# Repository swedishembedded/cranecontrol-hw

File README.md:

# CraneControl Schematic and PCB

**Electronic hardware for controlling a vehicle mounted movie production crane**

	Copyright (c) 2019-2022 Martin Schröder, All rights reserved.

- Connect with me on LinkedIn: https://www.linkedin.com/in/martinschroder/
- Connect by email: martin.schroder@swedishembedded.com

This repository contains electical schematic and pcb layouts for boards that
can be used to control a movie production camera crane.

What does such a crane look like in practice? Well here is CraneControl boards
providing HMI and dual motor control function to FlyingBergman movie production
crane (click on images to watch the video):

[](http://www.youtube.com/watch?v=k-2InPx5LMA
"FlyingBergman")

[](http://www.youtube.com/watch?v=5sOf54V7gs8
"FlyingBergman on land")

[](http://www.youtube.com/watch?v=lv9wT3cRuf8
"FlyingBergman at sea")

[FlyingBergman](https://flyingbergman.se) crane is best known for being used for filming all car scenes in
2022 Netflix series "Clark".

[](http://www.youtube.com/watch?v=Xm6EU1w8b1s
"Clark")

If you are a movie producer and would like to order finished product then send
an email to info@swedishembedded.com and ask for more information. The complete
FlyingBergman setup also includes the crane assembly, HMI control panel for
mounting inside the vehicle and all necessary electronics.

## CraneControl platform

FlyingBergman is only one specific application of crane control hardware
design. CraneControl was originally designed to be a versatile solution capable
of advanced features like field oriented control of 2 60V PMSM motors at the
same time using the same microcontroller. It was also designed to provide
modern communication options like CAN-FD and EtherCAT.

In the case of FlyingBergman only a subset of these features was used - meaning
there is a lot of room to epand the use of this hardware for achieving more
complex control tasks in an industrial environment.

## Block diagram

## Schematic PDF

## Who is this for

This repository is for you if:

- You are a student of embedded systems courses at swedishembedded.com
  (https://swedishembedded.com/tag/training).

- You are building industrial control solutions and you would like to add
  support for advanced motor control (in this case you can also contract this
  task to Swedish Embedded Consulting Group. Book a call here:
  https://swedishembedded.com/book-call)

- You are simply curious about designing practical hardware and would like to
  learn from this project.

## License

You may use this design as inspiration for other designs as long as you develop
schematic and layout by yourself. You may also use this design as learning
materials for study.

If you would like to build a commercial product using this design then you can
contract Swedish Embedded Consulting Group to implement a specialized
hardware/software solution for you (send and email to
info@swedishembedded.com).

## Building

To generate gerbers for this design from command line you can use kibot
(https://github.com/INTI-CMNB/KiBot) with provided 'motordriver-2x.kibot.yaml'
file in this repository.

You can also edit this design in KiCad (version 6.0 or above).

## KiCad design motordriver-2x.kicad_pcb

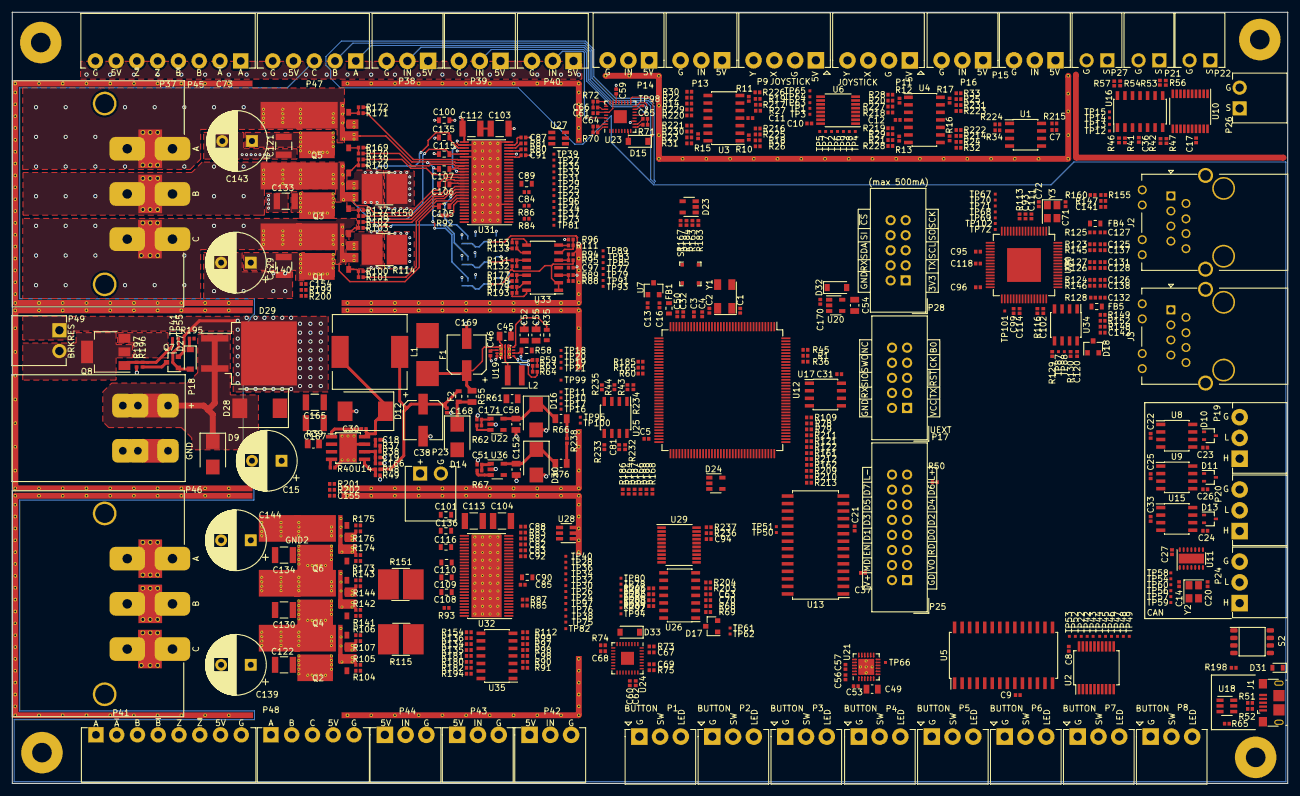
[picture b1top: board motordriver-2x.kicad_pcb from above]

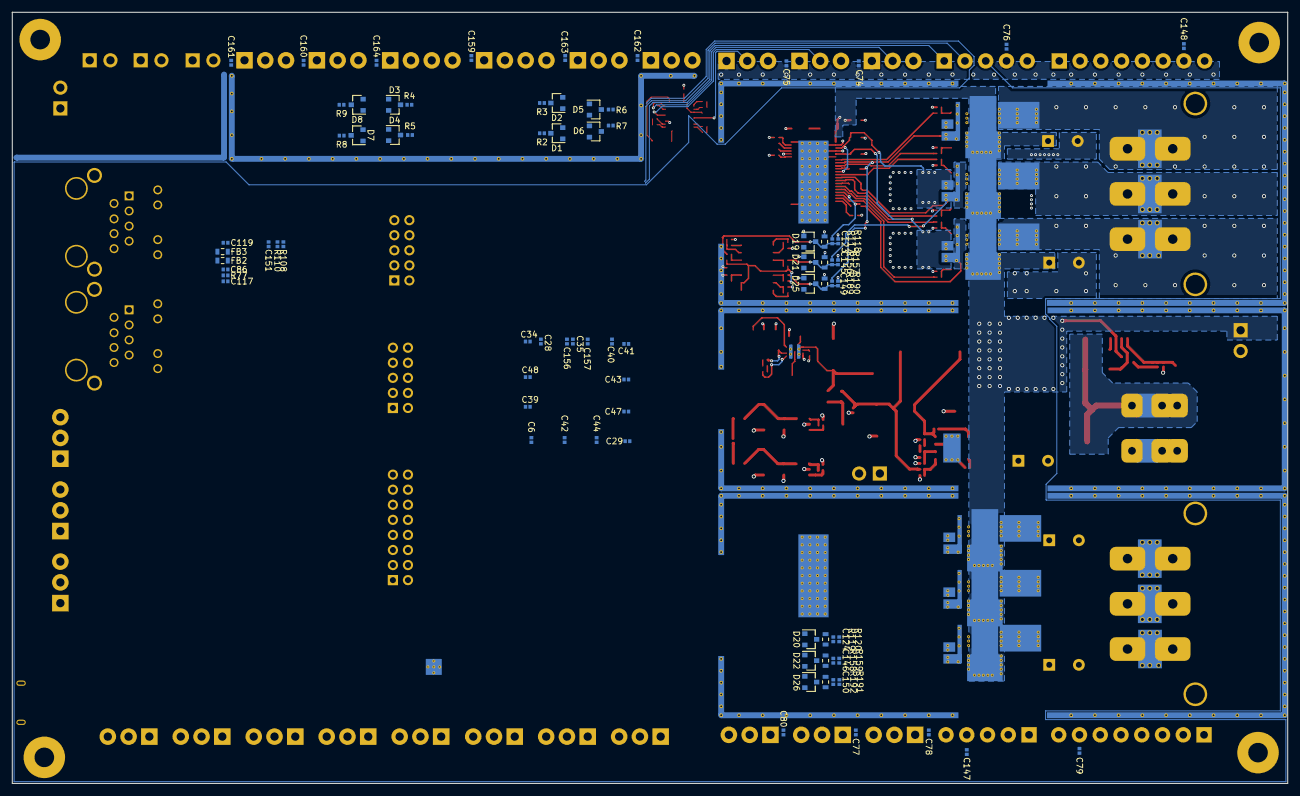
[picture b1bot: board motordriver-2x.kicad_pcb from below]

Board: 4 copper layers, 215.0 x 130.0 mm, 651 parts (79 on the bottom side), 453 nets.

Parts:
C1, C2, C14, C20, C71, C72, C125, C126, C127, C128, C131, C132, C137, C138: CAP_10pF_50V_0402; C_0402_1005Metric
C3, C4, C8, C9, C10, C11, C12, C16, C17, C21, C22, C23, C24, C25, C26, C27, C28, C29, C30, C31, C32, C33, C34, C35, C36, C39, C40, C41, C42, C43, C44, C46, C47, C48, C50, C59, C60, C61, C62, C63, C70, C82, C83, C86, C93, C94, C95, C96, C97, C98, C99, C102, C111, C114, C117, C118, C119, C120, C151, C154, C155, C156, C157: CAP_100nF_50V_0402; C_0402_1005Metric
C5, C6, C7, C13, C37, C51, C53, C56, C57, C73, C74, C75, C76, C77, C78, C79, C80, C81, C84, C85, C87, C88, C91, C92, C147, C148, C159, C160, C161, C162, C163, C164, C168, C170, C171: CAP_2.2uF_16V_0402; C_0402_1005Metric
C15, C139, C140, C143, C144: CAPP_220uF_63V_10x15_THT; CP_Radial_D10.0mm_P5.00mm
C18: CAP_27nF_16V_0402; C_0402_1005Metric
C19, C64, C65, C66, C67, C68, C69, C166: CAP_100pF_50V_0402; C_0402_1005Metric
C38, C169: CAPP_100uF_25V_6357; CP_Elec_6.3x5.7
C45, C49: CAP_10uF_25V_0805; C_0805_2012Metric
C52, C54, C55, C58, C152: CAP_22uF_10V_0805; C_0805_2012Metric
C89, C90: CAP_0.022uF_100V_0603; C_0603_1608Metric
C100, C101, C105, C106, C107, C108, C109, C110, C123, C124, C145, C146, C149, C150: CAP_100nF_100V_0603; C_0603_1608Metric
C103, C104, C112, C113, C121, C122, C129, C130, C133, C134, C165, C167: CAP_2.2uF_100V_1210; C_1210_3225Metric
C115, C116, C135, C136: CAP_1nF_100V_0603; C_0603_1608Metric
C141, C142: CAP_22nF_50V_0402; C_0402_1005Metric
D1, D2, D3, D4, D5, D6, D7, D8, D17, D18, D19, D20, D21, D22, D25, D26: D_BAT54S; SOT-23
D9: D_SMBJ48A; D_SMB
D10, D11, D13: D_ESDCAN03; SOT-323_SC-70
D12, D28: D_CDBC5100; D_SMC
D14: D_SMBJ12A; D_SMB
D15, D27, D32, D33: D_BAT54; D_SOD-123
D16, D30: D_SZ1SMB5913BT3G; D_SMB
D23, D24: D_TPD3E001; SOT-23-5
D29: D_STPS41H100; TO-263-2
D31: LED_RED_0603; LED_0603_1608Metric
F1: FUSE_3A_9750; Fuse_Littlefuse_9750
F2: FUSE_4A_0603; Fuse_0603_1608Metric
FB1, FB2, FB3, FB4, FB5: LB_220R_2A_0603; L_0603_1608Metric
GND1: GND_100X30
GND2, GND3: GND_MOTOR_DRIVER
GND4: GND_ANALOG_IN
GND5: GND_ANALOG_OUT
J1: USB_B_Micro; USB_Micro-B_GCT_USB3076-30-A
J2, J3: CONN_RJ45_MAG; RJ45_Tranformer
L1: L_33uH_4.2A_45mR; L_Wuerth_WE-PD-Typ-LS_1250x1250
L2: L_2.2uH_8A; L_Coilcraft_XxL4020
MT1, MT2, MT3, MT4: MOUNT_HOLE; MountingHole_3.2mm_M3_Pad
P1, P2, P3, P4, P5, P6, P7, P8: CONN_BUTTON
P9, P11: CONN_JOYSTICK
P13, P14, P15, P16, P38, P39, P40, P42, P43, P44: CONN_SENSOR
P17: CONN_DEBUG_2R; IDC-Header_2x05_P2.54mm_Vertical
P18: CONN_POWER_41A; PhoenixContact_Power41A_2,5_2-G-7,62_1x02_P7.62mm_Horizontal
P19, P20, P24: CONN_CAN
P21, P22, P26, P27: CONN_AN_OUT
P23: CONN_POWER_10A
P25: CONN_LCD
P28: CONN_UEXT
P37, P41: CONN_ENCODER
P45, P46: CONN_MOTOR; ANYTEK_7.62mm_2x_3P_32A
P47, P48: CONN_HALL
P49: CONN_BRKRES
Q1, Q2, Q3, Q4, Q5, Q6: Q_NMOS_2X_60V_63A; PowerPack-8x8-Dual
Q7: Q_PNP_BC856; SOT-23
Q8: Q_NMOS_BUK9875; SOT-223
R1, R2, R3, R4, R5, R6, R7, R8, R9, R38, R41, R42, R43, R44, R49, R53, R54, R60, R62, R63, R64, R67, R84, R85, R86, R87, R88, R89, R90, R91, R94, R95, R96, R97, R98, R99, R100, R103, R104, R107, R108, R110, R113, R116, R118, R120, R131, R132, R133, R134, R135, R136, R137, R140, R141, R144, R149, R157, R159, R160, R169, R172, R173, R176, R177, R178, R179, R180, R181, R182, R183, R184, R185, R186, R187, R188, R190, R192, R195, R196, R197, R199, R201, R203, R204, R205, R206, R207, R208: RES_10K_1%_0402; R_0402_1005Metric
R10, R11, R12, R13, R14, R15, R16, R17, R65, R147, R148: RES_0R_0402; R_0402_1005Metric
R18, R19, R20, R21, R22, R23, R24, R25: RES_1K5_1%_0402; R_0402_1005Metric
R26, R27, R28, R29, R30, R31, R32, R33, R36, R37, R45, R59, R80, R81, R82, R83, R129, R130: RES_3K_1%_0402; R_0402_1005Metric
R34, R214, R215, R216, R217, R218, R219, R220, R221, R222, R223, R224, R225, R226, R227, R228, R229, R230, R231, R232, R233, R234, R235, R236, R237, R238: RES_NOFIT_0402; R_0402_1005Metric
R35, R58: RES_147k_1%_0603; R_0603_1608Metric
R39, R55, R61, R66, R76: RES_10mOhm_1%; R_0805_2012Metric
R40, R48, R68, R117, R119, R156, R158, R189, R191: RES_137K_1%_0402; R_0402_1005Metric
R46, R47, R56, R57, R69, R111, R112, R153, R154, R163, R164, R165, R166, R167, R168, R193, R194: RES_5K_1%_0402; R_0402_1005Metric
R50, R198: RES_470R_1%_0402; R_0402_1005Metric
R51, R52, R101, R102, R105, R106, R138, R139, R142, R143, R170, R171, R174, R175: RES_22R_1%_0402; R_0402_1005Metric
R70, R71, R72, R73, R74, R75, R78, R79, R109, R121, R122, R152, R155, R161, R162, R209, R210, R211, R212, R213: RES_270R_1%_0402; R_0402_1005Metric
R77: RES_12.1K_1%_0402; R_0402_1005Metric
R92, R93: RES_1M_1%_0402; R_0402_1005Metric
R114, R115, R150, R151: RES_5mR_1%_10W; R_2818_7146Metric
R123, R124, R125, R126, R127, R128, R145, R146: RES_49.9_0.1%_0402; R_0402_1005Metric
R200, R202: RES_NTC_10K_402; R_0402_1005Metric
S1: SW_BTN_3.7x3.7; SW_PTS540
S2: SW_DIP_4P; SOIC127P670X145-8N
TP1, TP2, TP3, TP4, TP5, TP6, TP7, TP8, TP9, TP10, TP11, TP12, TP13, TP14, TP15, TP16, TP17, TP18, TP19, TP20, TP21, TP22, TP23, TP24, TP25, TP26, TP27, TP28, TP29, TP30, TP31, TP32, TP33, TP34, TP35, TP36, TP37, TP38, TP39, TP40, TP41, TP42, TP43, TP44, TP45, TP46, TP47, TP48, TP49, TP50, TP51, TP52, TP53, TP54, TP55, TP56, TP57, TP58, TP59, TP60, TP61, TP62, TP63, TP64, TP65, TP66, TP67, TP68, TP69, TP70, TP71, TP72, TP73, TP74, TP75, TP76, TP77, TP78, TP79, TP80, TP81, TP82, TP83, TP84, TP85, TP86, TP87, TP88, TP89, TP90, TP91, TP92, TP93, TP94, TP95, TP96, TP97, TP98, TP99, TP100, TP101, TP102: Test_Point; TestPoint_Pad_0.5x0.5mm
U1, U25: IC_MIC2026; SOIC-8_3.9x4.9mm_P1.27mm
U2: IC_MAX6818; SSOP-20_5.3x7.2mm_P0.65mm
U3, U4, U16, U26, U33, U35: IC_TLV2474; SOIC-14_3.9x8.7mm_P1.27mm
U5, U13: IC_MCP23S17; SOIC-28W_7.5x17.9mm_P1.27mm
U6: IC_SN74LV4051; TSSOP-16_4.4x5mm_P0.65mm
U7: IC_NCP51460SN33T1G; SOT-23
U8, U9, U15: IC_TJA1044GT3; SOIC-8_3.9x4.9mm_P1.27mm
U10, U29: IC_MCP4461; TSSOP-20_4.4x6.5mm_P0.65mm
U11: IC_MCP2517FD-xJHA; DFN-14-1EP_3x4.5mm_P0.65mm_EP1.65x4.25mm
U12: IC_STM32F429ZET6; LQFP-144_20x20mm_P0.5mm
U14: IC_TPS54360DDA; TI_SO-PowerPAD-8
U17, U34: IC_M24C16; SOIC-8_3.9x4.9mm_P1.27mm
U18, U27, U28: IC_USBLC6-2; SOT-23-6L
U19: IC_TPS62147RGXR; RGX_VQFN-11
U20, U22, U36: IC_TLV75533; SOT-23-5
U21: IC_LP55231; WQFN-24-1EP_4x4mm_P0.5mm_EP2.7x2.7mm_Thermal
U23, U24: IC_MAX14890; QFN-32-1EP_5x5mm_P0.5mm_EP2.20x2.20mm
U30: IC_LAN9252; TQFP-64-1EP_10x10mm_P0.5mm_EP5.7x5.7mm
U31, U32: IC_DRV8302; HTSSOP-56-PowerPAD_6.2x14.1mm_P0.5mm_EP3.61x6.35mm
Y1: XTAL_8Mhz_5032; Crystal_ABM3B_5032-4Pin_5.0x3.2mm
Y2: XTAL_20MHz_3225; Crystal_SMD_3225-4Pin_3.2x2.5mm
Y3: XTAL_25MHz_3225; Crystal_SMD_3225-4Pin_3.2x2.5mm

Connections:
AINPWEN: R224.2, U1.1, U12.12
AIN_OC: R34.1, U1.2, U5.21
AIN_VDD_5V: C159.1, C160.1, C161.1, C162.1, C163.1, C164.1, P9.1, P11.1, P13.1, P14.1, P15.1, P16.1, R215.1, U1.8
AP_RESET1: U5.25, U10.15
AP_SCL1: R45.1, U10.5, U12.139, U17.6, U21.9, U29.5
AP_SDA1: R36.1, U10.6, U12.137, U17.5, U21.8, U29.6
AP_WP1: U5.24, U10.14
BLED_EN: U12.58, U21.5
BLED_INT: U12.67, U21.7
BOOT0: P17.9, R1.2, U12.138
CANFD_CS: TP60.1, U11.13, U12.125
CANFD_INT: TP59.1, U11.4, U12.124
CANFD_MISO: TP70.1, U11.12, U12.127, U30.13
CANFD_MOSI: TP69.1, U11.11, U12.129, U30.17
CANFD_SCK: TP72.1, U11.10, U12.128, U30.19
CANFD_SOF: U11.3, U12.93
CAN_RX1: U8.4, U12.114
CAN_RX2: U9.4, U12.73
CAN_TX1: U8.1, U12.115
CAN_TX2: U9.1, U12.74
DC_CAL1: TP74.1, U12.89, U31.12
DC_CAL2: TP76.1, U12.90, U32.12
ECAT_CS: TP71.1, U12.126, U30.50
ECAT_IRQ: TP68.1, U12.92, U30.44
ECAT_RESET: TP67.1, U12.91, U30.11
EE_WEN: U12.140, U17.7
ENC1VDD5V: C73.2, C74.2, C75.2, C76.2, C148.1, P37.7, P38.1, P39.1, P40.1, P47.4, R232.1, U25.8
ENC2VDD5V: C77.2, C78.2, C79.2, C80.2, C147.1, P41.7, P42.1, P43.1, P44.1, P48.4, R233.1, U25.5
ENCA1: U12.110, U23.1
ENCA2: U12.81, U24.1
ENCB1: U12.133, U23.8
ENCB2: U12.82, U24.8
ENCCS1: U12.118, U23.4
ENCCS2: U12.86, U24.4
ENCMISO1: R121.1, U23.3
ENCMISO2: R122.1, U24.3
ENCMOSI1: R162.1, U23.6
ENCMOSI2: R209.1, U24.6
ENCOC1: R43.2, U5.22, U25.2
ENCOC2: R44.2, U5.23, U25.3
ENCPWEN1: R234.2, U12.69, U25.1
ENCPWEN2: R235.2, U12.70, U25.4
ENCSCK1: R78.1, U23.5
ENCSCK2: R79.1, U24.5
ENCSH1: U12.119, U23.28
ENCSH2: U12.80, U24.28
ENCZ1: U12.77, U23.24
ENCZ2: U12.85, U24.24
EN_GATE1: TP96.1, U12.117, U31.16
EN_GATE2: TP97.1, U12.116, U32.16
FAULT1: R86.1, U12.122, U31.6
FAULT2: R87.1, U12.123, U32.6
GA1_N: R102.2, U31.45
GA1_P: R101.2, U31.47
GAIN1: TP73.1, U12.53, U31.10
GAIN2: TP75.1, U12.55, U32.10
GB1_N: R139.2, U31.40
GB1_P: R138.2, U31.42
GC1_N: R171.2, U31.35
GC1_P: R170.2, U31.37
GHA2: R105.2, U32.47
GHB2: R142.2, U32.42
GHC2: R174.2, U32.37
GLA2: R106.2, U32.45
GLB2: R143.2, U32.40
GLC2: R175.2, U32.35
GND: C1.2, C2.2, C3.2, C4.2, C5.2, C6.2, C7.2, C8.2, C9.2, C10.1, C11.1, C12.1, C13.2, C14.1, C15.2, C16.2, C17.1, C18.2, C19.2, C20.2, C21.2, C22.1, C23.1, C24.1, C25.1, C26.1, C27.1, C28.2, C29.2, C31.1, C32.2, C33.2, C34.2, C35.2, C36.1, C37.2, C38.2, C39.2, C40.2, C41.2, C42.2, C43.2, C44.2, C45.2, C46.2, C47.2, C48.2, C49.2, C50.2, C51.1, C52.2, C54.2, C55.2, C57.2, C58.2, C59.2, C60.2, C61.2, C62.2, C63.2, C70.1, C71.1, C72.1, C73.1, C74.1, C75.1, C76.1, C77.1, C78.1, C79.1, C80.1, C81.2, C82.2, C83.2, C84.2, C85.2, C86.1, C87.2, C88.2, C91.2, C92.2, C93.2, C94.1, C95.2, C96.2, C97.1, C98.1, C99.2, C100.2, C101.2, C102.2, C103.2, C104.2, C111.2, C114.2, C115.2, C116.2, C117.1, C118.2, C119.2, C120.1, C121.2, C122.2, C123.2, C124.2, C125.1, C126.2, C127.1, C128.2, C129.2, C130.2, C131.1, C132.2, C133.2, C134.2, C135.2, C136.2, C137.1, C138.2, C139.2, C140.2, C141.2, C142.1, C143.2, C144.2, C145.2, C146.2, C147.2, C148.2, C149.2, C150.2, C151.2, C152.2, C154.1, C155.1, C156.1, C157.1, C159.2, C160.2, C161.2, C162.2, C163.2, C164.2, C165.2, C166.2, C167.2, C168.2, C169.2, C170.2, C171.1, D1.1, D2.1, D3.1, D4.1, D5.1, D6.1, D7.1, D8.1, D9.2, D10.3, D11.3, D12.2, D13.3, D14.2, D16.2, D17.1, D19.1, D20.1, D21.1, D22.1, D23.3, D24.3, D25.1, D26.1, D30.2, D31.1, GND1.1, GND2.1, GND3.1, GND4.1, GND5.1, J1.5, J1.6, J2.8, J2.9, J3.8, J3.9, P1.1, P2.1, P3.1, P4.1, P5.1, P6.1, P7.1, P8.1, P9.2, P11.2, P13.3, P14.3, P15.3, P16.3, P17.2, P18.2, P19.3, P20.3, P21.2, P22.2, P23.2, P24.3, P25.1, P25.16, P26.2, P27.2, P28.2, P37.8, P38.3, P39.3, P40.3, P41.8, P42.3, P43.3, P44.3, P47.5, P48.5, Q5.3, Q6.3, Q8.3, R1.1, R26.2, R27.2, R28.2, R29.2, R30.2, R31.2, R32.2, R33.2, R40.2, R41.2, R42.2, R49.2, R53.2, R54.2, R60.2, R64.2, R69.1, R77.2, R89.1, R91.1, R92.1, R93.1, R96.2, R99.2, R100.2, R103.2, R104.2, R107.2, R108.1, R110.1, R113.1, R114.1, R115.1, R116.1, R118.1, R120.1, R133.2, R136.2, R137.2, R140.2, R141.2, R144.2, R149.1, R150.2, R151.2, R157.1, R159.1, R160.1, R169.2, R172.2, R173.2, R176.2, R179.2, R182.2, R183.1, R184.1, R185.1, R186.1, R187.1, R188.1, R190.1, R192.1, R197.2, R200.2, R202.2, R204.1, R206.1, R208.1, R214.1, R225.1, R226.1, R227.1, R228.1, R229.1, R230.1, R231.1, S1.1, S1.2, S2.1, S2.2, S2.3, S2.4, U1.6, U2.10, U3.11, U4.11, U5.10, U5.15, U5.16, U5.17, U6.6, U6.7, U6.8, U7.3, U8.2, U8.8, U9.2, U9.8, U10.3, U10.4, U10.7, U10.8, U10.13, U10.16, U10.18, U11.7, U11.15, U12.16, U12.31, U12.38, U12.51, U12.61, U12.83, U12.94, U12.107, U12.120, U12.130, U13.10, U13.15, U13.16, U13.17, U14.7, U14.9, U15.2, U16.11, U17.1, U17.2, U17.3, U17.4, U18.2, U19.3, U19.4, U19.10, U19.11, U20.2, U21.4, U21.6, U21.10, U21.20, U21.21, U21.25, U22.2, U23.11, U23.33, U24.11, U24.33, U25.6, U26.11, U27.2, U28.2, U29.3, U29.7, U29.8, U29.13, U29.16, U29.18, U30.4, U30.41, U30.65, U31.7, U31.8, U31.28, U31.30, U31.32, U31.34, U31.57, U32.7, U32.8, U32.28, U32.30, U32.32, U32.34, U32.57, U33.11, U34.1, U34.2, U34.3, U34.4, U34.7, U35.11, U36.2
GPEX_CS: U12.136, U13.11
GPEX_INTA: TP50.1, U12.21, U13.20
GPEX_INTB: TP51.1, U12.22, U13.19
GPEX_MISO: R212.1, U13.14
GPEX_MOSI: R213.1, U13.13
GPEX_RESET: U12.49, U13.18
GPEX_SCK: R211.1, U13.12
GPIO_CS: U5.11, U12.88
GPIO_INTA: TP52.1, U5.20, U12.57
GPIO_INTB: TP53.1, U5.19, U12.87
GPIO_MISO: R161.1, U5.14
GPIO_MOSI: R210.1, U5.13
GPIO_RESET: U5.18, U12.56
GPIO_SCK: R109.1, U5.12
HALL_A1: D23.1, R163.2, R183.2, U12.134
HALL_A2: D24.1, R164.2, R186.2, U12.34
HALL_B1: D23.2, R167.2, R184.2, U12.135
HALL_B2: D24.2, R166.2, R187.2, U12.35
HALL_C1: D23.4, R165.2, R185.2, U12.46
HALL_C2: D24.4, R168.2, R188.2, U12.36
INHA1: TP23.1, U12.60, U31.17
INHA2: TP24.1, U12.96, U32.17
INHB1: TP29.1, U12.64, U31.19
INHB2: TP30.1, U12.97, U32.19
INHC1: TP33.1, U12.66, U31.21
INHC2: TP34.1, U12.98, U32.21
INLA1: TP25.1, U12.59, U31.18
INLA2: TP26.1, U12.43, U32.18
INLB1: TP31.1, U12.63, U31.20
INLB2: TP32.1, U12.75, U32.20
INLC1: TP35.1, U12.65, U31.22
INLC2: TP36.1, U12.76, U32.22
LCD_D0: P25.7, U13.1
LCD_D1: P25.8, U13.2
LCD_D2: P25.9, U13.3
LCD_D3: P25.10, U13.4
LCD_D4: P25.11, U13.5
LCD_D5: P25.12, U13.6
LCD_D6: P25.13, U13.7
LCD_D7: P25.14, U13.8
LCD_EN: P25.6, U13.23
LCD_LED: R50.2, U13.24
LCD_MDATA: P25.4, U13.21
LCD_READ: P25.5, U13.22
LCD_VO: P25.3, U29.9
LED_OUT1: P1.3, U21.19
LED_OUT2: P2.3, U21.18
LED_OUT3: P3.3, U21.17
LED_OUT4: P4.3, U21.16
LED_OUT5: P5.3, U21.15
LED_OUT6: P6.3, U21.14
LED_OUT7: P7.3, U21.13
LED_OUT8: P8.3, U21.12
MOC1: U12.50, U31.9
MOC2: U12.54, U32.9
MOCP_RESET: U5.26, U29.15
MOCP_WP: U5.27, U29.14
MOTOR1_BRKIN: D15.2, U12.68, U23.7
MOTOR2_BRKIN: D33.2, U12.42, U24.7
NRST: C4.1, P17.5, S1.3, S1.4, U12.25
unnamed: C1.1, U12.23, Y1.1
unnamed: C2.1, U12.24, Y1.3
unnamed: C5.1, U12.71
unnamed: C6.1, U12.106
unnamed: C14.2, U11.5, Y2.1
unnamed: C15.1, D28.1, R39.2, TP10.1
unnamed: C18.1, R37.2
unnamed: C20.1, U11.6, Y2.3
unnamed: C30.1, D12.1, L1.1, U14.8
unnamed: C30.2, U14.1
unnamed: C32.1, C50.1, FB1.2, U12.32, U12.33
unnamed: C46.1, U19.9
unnamed: C52.1, C55.1, L2.2, R35.1, R58.1, R61.2, TP19.1, U19.6
unnamed: C53.1, U21.1
unnamed: C53.2, U21.23
unnamed: C54.1, D32.2, P28.1, U20.5
unnamed: C56.1, U21.24
unnamed: C56.2, U21.2
unnamed: C57.1, U21.22
unnamed: C58.1, D16.1, R66.2, TP21.1, U22.5
unnamed: C63.1, D17.3, R68.2, R69.2, TP61.1, U26.3
unnamed: C64.1, R70.2
unnamed: C64.2, P37.2, U23.31
unnamed: C65.1, R71.2
unnamed: C65.2, P37.4, U23.10
unnamed: C66.1, R72.2
unnamed: C66.2, P37.6, U23.26
unnamed: C67.1, R73.2
unnamed: C67.2, P41.2, U24.31
unnamed: C68.1, R74.2
unnamed: C68.2, P41.4, U24.10
unnamed: C69.1, R75.2
unnamed: C69.2, P41.6, U24.26
unnamed: C71.2, U30.1, Y3.3
unnamed: C72.2, U30.2, Y3.1
unnamed: C84.1, U31.13
unnamed: C85.1, U32.13
unnamed: C86.2, FB2.1, U30.58
unnamed: C87.1, U31.27
unnamed: C88.1, U32.27
unnamed: C89.1, U31.15
unnamed: C89.2, U31.14
unnamed: C90.1, U32.15
unnamed: C90.2, U32.14
unnamed: C91.1, U31.23
unnamed: C92.1, U32.23
unnamed: C103.1, C112.2
unnamed: C104.1, C113.2
unnamed: C105.1, U31.48
unnamed: C106.1, U31.43
unnamed: C107.1, U31.38
unnamed: C108.1, U32.48
unnamed: C109.1, U32.43
unnamed: C110.1, U32.38
unnamed: C114.1, C118.1, C151.1, FB3.2, U30.6, U30.24, U30.38
unnamed: C117.2, FB5.2, R124.2, R126.2, R128.2, R146.2, R148.1, U30.51
unnamed: C119.1, FB4.1, R123.1, R125.1, R127.1, R145.1, R147.2, U30.64
unnamed: C120.2, D18.3, U34.8
unnamed: C125.2, J2.1, R123.2, U30.62
unnamed: C126.1, J3.6, R124.1, U30.54
unnamed: C127.2, J2.3, R125.2, U30.63
unnamed: C128.1, J3.4, R126.1, U30.55
unnamed: C131.2, J2.4, R127.2, U30.60
unnamed: C132.1, J3.3, R128.1, U30.52
unnamed: C137.2, J2.6, R145.2, U30.61
unnamed: C138.1, J3.1, R146.1, U30.53
unnamed: C141.1, J2.2, J2.5, R147.1
unnamed: C142.2, J3.2, J3.5, R148.2
unnamed: C152.1, D30.1, R76.2, TP99.1, U36.5
unnamed: C165.1, C167.1, R39.1, TP11.1, U14.2
unnamed: C19.1, C166.1, R38.1, U14.6
unnamed: C38.1, C168.1, F2.2, L1.2, R48.1
unnamed: C45.1, C169.1, F1.1, R55.2, TP16.1, U19.1, U19.8
unnamed: D1.3, R2.1, R216.2, U3.3
unnamed: D2.3, R3.1, R217.2, U3.5
unnamed: D3.3, R4.1, R218.2, U4.3
unnamed: D4.3, R5.1, R219.2, U4.5
unnamed: D5.3, R6.1, R220.2, U3.10
unnamed: D6.3, R7.1, R221.2, U3.12
unnamed: D7.3, R8.1, R222.2, U4.10
unnamed: D8.3, R9.1, R223.2, U4.12
unnamed: D10.1, P19.2, U8.7
unnamed: D10.2, P19.1, U8.6
unnamed: D11.1, P20.2, U9.7
unnamed: D11.2, P20.1, U9.6
unnamed: D13.1, P24.2, U15.7
unnamed: D13.2, P24.1, U15.6
unnamed: D14.1, F2.1, R55.1, TP17.1
unnamed: D15.1, U23.17
unnamed: D27.1, R195.1
unnamed: D27.2, Q7.1, TP55.1
unnamed: D31.2, R198.2
unnamed: D33.1, U24.17
unnamed: F1.2, P23.1
unnamed: FB3.1, U30.56, U30.59
unnamed: J1.1, R65.2, U18.5
unnamed: J1.2, R52.2
unnamed: J1.3, R51.2
unnamed: J2.10, R155.1
unnamed: J3.10, R152.1
unnamed: L2.1, U19.2
unnamed: P9.3, R2.2
unnamed: P9.4, R3.2
unnamed: P11.3, R4.2
unnamed: P11.4, R5.2
unnamed: P13.2, R6.2
unnamed: P14.2, R7.2
unnamed: P15.2, R8.2
unnamed: P16.2, R9.2
unnamed: P21.1, R46.1, U16.1
unnamed: P22.1, R47.1, U16.7
unnamed: P25.15, R50.1
unnamed: P26.1, R56.1, U16.8
unnamed: P27.1, R57.1, U16.14
unnamed: P37.1, R70.1, U23.32
unnamed: P37.3, R71.1, U23.9
unnamed: P37.5, R72.1, U23.25
unnamed: P38.2, U23.16
unnamed: P39.2, U23.13
unnamed: P40.2, U23.29
unnamed: P41.1, R73.1, U24.32
unnamed: P41.3, R74.1, U24.9
unnamed: P41.5, R75.1, U24.25
unnamed: P42.2, U24.16
unnamed: P43.2, U24.13
unnamed: P44.2, U24.29
unnamed: P47.1, R163.1
unnamed: P47.2, R167.1
unnamed: P47.3, R165.1
unnamed: P48.1, R164.1
unnamed: P48.2, R166.1
unnamed: P48.3, R168.1
unnamed: P49.2, Q8.2, Q8.4
unnamed: Q1.1, R100.1, R101.1
unnamed: Q1.4, R102.1, R103.1
unnamed: Q2.1, R104.1, R105.1
unnamed: Q2.4, R106.1, R107.1
unnamed: Q3.1, R137.1, R138.1
unnamed: Q3.4, R139.1, R140.1
unnamed: Q4.1, R141.1, R142.1
unnamed: Q4.4, R143.1, R144.1
unnamed: Q5.1, R169.1, R170.1
unnamed: Q5.4, R171.1, R172.1
unnamed: Q6.1, R173.1, R174.1
unnamed: Q6.4, R175.1, R176.1
unnamed: Q7.3, R196.2
unnamed: Q8.1, R196.1, R197.1, TP41.1
unnamed: R10.1, R18.2, R216.1, R225.2, U3.1
unnamed: R10.2, U3.2
unnamed: R11.1, R19.2, R217.1, R226.2, U3.7
unnamed: R11.2, U3.6
unnamed: R12.1, R20.2, R218.1, R227.2, U4.1
unnamed: R12.2, U4.2
unnamed: R13.1, R21.2, R219.1, R228.2, U4.7
unnamed: R13.2, U4.6
unnamed: R14.1, R22.2, R220.1, R229.2, U3.8
unnamed: R14.2, U3.9
unnamed: R15.1, R23.2, R221.1, R230.2, U3.14
unnamed: R15.2, U3.13
unnamed: R16.1, R24.2, R214.2, R222.1, U4.8
unnamed: R16.2, U4.9
unnamed: R17.1, R25.2, R223.1, R231.2, U4.14
unnamed: R17.2, U4.13
unnamed: R18.1, R26.1, TP7.1, U6.13
unnamed: R19.1, R27.1, TP5.1, U6.14
unnamed: R20.1, R28.1, TP3.1, U6.15
unnamed: R21.1, R29.1, TP1.1, U6.12
unnamed: R22.1, R30.1, TP2.1, U6.1
unnamed: R23.1, R31.1, TP4.1, U6.5
unnamed: R24.1, R32.1, TP6.1, U6.2
unnamed: R25.1, R33.1, TP8.1, U6.4
unnamed: R35.2, TP18.1, U19.7
unnamed: R37.1, R38.2
unnamed: R40.1, U14.4
unnamed: R41.1, R46.2, U16.2
unnamed: R42.1, R47.2, U16.6
unnamed: R48.2, R49.1, U14.5
unnamed: R51.1, U18.6
unnamed: R52.1, U18.4
unnamed: R53.1, R56.2, U16.9
unnamed: R54.1, R57.2, U16.13
unnamed: R58.2, R59.2, U19.5
unnamed: R59.1, R63.2
unnamed: R60.1, U12.48
unnamed: R62.1, U22.3
unnamed: R63.1, R64.1
unnamed: R67.1, U36.3
unnamed: R77.1, U30.57
unnamed: R80.1, U31.25
unnamed: R80.2, TP27.1, U27.6
unnamed: R81.1, U31.26
unnamed: R81.2, TP39.1, U27.4
unnamed: R82.1, U32.25
unnamed: R82.2, TP28.1, U28.6
unnamed: R83.1, U32.26
unnamed: R83.2, TP40.1, U28.4
unnamed: R88.1, R89.2, U33.3
unnamed: R90.1, R91.2, U35.3
unnamed: R92.2, U31.49
unnamed: R93.2, U32.49
unnamed: R94.1, R95.2, TP79.1, U33.5
unnamed: R97.1, R98.2, TP80.1, U35.5
unnamed: R108.2, U30.10
unnamed: R78.2, R79.2, R109.2, R211.2, U12.111
unnamed: R110.2, U30.9
unnamed: R96.1, R111.2, U33.6
unnamed: R99.1, R112.2, U35.6
unnamed: R113.2, U30.8
unnamed: R116.2, U30.45
unnamed: R121.2, R122.2, R161.2, R212.2, U12.112
unnamed: R129.2, TP87.1, U30.42, U34.5
unnamed: R130.2, TP88.1, U30.43, U34.6
unnamed: R131.1, R132.2, TP85.1, U33.10
unnamed: R95.1, R132.1, R178.1, TP77.1, U33.1, U33.2
unnamed: R133.1, R153.2, U33.9
unnamed: R134.1, R135.2, TP86.1, U35.10
unnamed: R98.1, R135.1, R181.1, TP78.1, U35.1, U35.2
unnamed: R136.1, R154.2, U35.9
unnamed: R149.2, R152.2, U30.48
unnamed: R155.2, R160.2, U30.46
unnamed: R162.2, R209.2, R210.2, R213.2, U12.113
unnamed: R177.1, R178.2, TP91.1, U33.12
unnamed: R179.1, R193.2, U33.13
unnamed: R180.1, R181.2, TP92.1, U35.12
unnamed: R182.1, R194.2, U35.13
unnamed: R198.1, U12.100
unnamed: R203.1, R204.2, U26.5
unnamed: R205.1, R206.2, U26.10
unnamed: R207.1, R208.2, U26.12
unnamed: S2.5, U13.28
unnamed: S2.6, U13.27
unnamed: S2.7, U13.26
unnamed: S2.8, U13.25
unnamed: TP12.1, U10.2, U16.3
unnamed: TP13.1, U10.19, U16.5
unnamed: TP14.1, U10.12, U16.10
unnamed: TP15.1, U10.9, U16.12
unnamed: TP54.1, U11.8
unnamed: TP56.1, U11.1, U15.1
unnamed: TP57.1, U11.2, U15.4
unnamed: TP58.1, U11.9, U15.8
unnamed: TP66.1, U21.11
unnamed: TP98.1, U23.15
unnamed: TP101.1, U30.34
unnamed: TP102.1, U30.18
unnamed: U26.6, U26.7
unnamed: U26.8, U26.9
unnamed: U26.13, U26.14
OCW1: R84.1, U12.78, U31.5
OCW2: R85.1, U12.79, U32.5
OC_ADJ1: R236.1, TP37.1, U29.19, U31.11
OC_ADJ2: R237.1, TP38.1, U29.2, U32.11
POTADDRA: TP63.1, U6.11, U12.7
POTADDRB: TP64.1, U6.10, U12.8
POTADDRC: TP65.1, U6.9, U12.9
POT_MUX: TP9.1, U6.3, U12.14
PWM_IN1: U12.18, U23.12
PWM_IN2: U12.19, U24.12
SHA1: C105.2, P45.3, Q1.2, Q1.5, R117.1, U31.46
SHA2: C108.2, P46.3, Q2.2, Q2.5, R119.1, U32.46
SHB1: C106.2, P45.2, Q3.2, Q3.5, R156.1, U31.41
SHB2: C109.2, P46.2, Q4.2, Q4.5, R158.1, U32.41
SHC1: C107.2, P45.1, Q5.2, Q5.5, R189.1, U31.36
SHC2: C110.2, P46.1, Q6.2, Q6.5, R191.1, U32.36
SLA1: C115.1, Q1.3, R114.2, U31.33, U31.44
SLA2: C116.1, Q2.3, R115.2, U32.33, U32.44
SLB1: C135.1, Q3.3, R150.1, U31.31, U31.39
SLB2: C136.1, Q4.3, R151.1, U32.31, U32.39
SOA1: U12.37, U27.1
SOA2: U12.41, U28.1
SOB1: U12.40, U27.3
SOB2: U12.47, U28.3
SW1: TP22.1, U2.19, U5.1
SW2: TP42.1, U2.18, U5.2
SW3: TP43.1, U2.17, U5.3
SW4: TP44.1, U2.16, U5.4
SW5: TP45.1, U2.15, U5.5
SW6: TP46.1, U2.14, U5.6
SW7: TP47.1, U2.13, U5.7
SW8: TP48.1, U2.12, U5.8
SWCLK: P17.7, U12.109
SWDIO: P17.6, U12.105
SWEN: U2.1, U12.99
SWIRQ: TP49.1, U2.11, U12.132
SW_IN1: P1.2, U2.2
SW_IN2: P2.2, U2.3
SW_IN3: P3.2, U2.4
SW_IN4: P4.2, U2.5
SW_IN5: P5.2, U2.6
SW_IN6: P6.2, U2.7
SW_IN7: P7.2, U2.8
SW_IN8: P8.2, U2.9
TEMP_MOT1: C156.2, R199.2, R200.1, TP81.1, U12.15
TEMP_MOT2: C157.2, R201.2, R202.1, TP82.1, U12.20
UART1_RX: P17.4, U12.102
UART1_TX: P17.3, U12.101
UEXT_CS: P28.10, U12.3
UEXT_MISO: P28.7, U12.4
UEXT_MOSI: P28.8, U12.5
UEXT_PWEN: U12.2, U20.3
UEXT_RX: P28.4, U12.141
UEXT_SCK: P28.9, U12.1
UEXT_SCL: P28.5, U12.11
UEXT_SDA: P28.6, U12.10
UEXT_TX: P28.3, U12.142
USB_5V: C7.1, C11.2, C12.2, C13.1, C22.2, C25.2, C33.1, C36.2, C51.2, C61.1, C62.1, C81.1, C170.1, C171.2, D1.2, D2.2, D3.2, D4.2, D5.2, D6.2, D7.2, D8.2, D32.1, P17.1, R61.1, R62.2, R65.1, R67.2, R215.2, R232.2, R233.2, TP20.1, U1.7, U3.4, U4.4, U7.1, U8.3, U9.3, U15.3, U16.4, U20.1, U22.1, U23.23, U23.27, U24.23, U24.27, U25.7, U36.1
USB_N: U12.103, U18.3
USB_P: U12.104, U18.1
VDD_3V3: C8.1, C9.1, C10.2, C17.2, C21.1, C23.2, C24.2, C26.2, C27.2, C31.2, C37.1, C49.1, C70.2, C93.1, C94.2, C95.1, C96.1, C97.2, C98.2, C99.1, C102.1, C111.1, C154.2, C155.2, D17.2, D18.1, D19.2, D20.2, D21.2, D22.2, D23.5, D24.5, D25.2, D26.2, FB2.2, FB4.2, FB5.1, P25.2, R66.1, R88.2, R90.2, R129.1, R130.1, R199.1, R201.1, R203.2, R205.2, R207.2, R236.2, R237.2, R238.2, TP95.1, U2.20, U5.9, U6.16, U8.5, U9.5, U10.1, U10.10, U10.11, U10.17, U10.20, U11.14, U13.9, U15.5, U17.8, U21.3, U26.4, U29.1, U29.4, U29.10, U29.17, U29.20, U30.5, U30.7, U30.14, U30.20, U30.32, U30.37, U30.47, U33.4, U35.4
VDD_3V3_MCU: C3.1, C28.1, C29.1, C34.1, C35.1, C39.1, C40.1, C41.1, C42.1, C43.1, C44.1, C47.1, C48.1, C59.1, C60.1, R34.2, R36.2, R43.1, R44.1, R45.2, R76.1, R84.2, R85.2, R86.2, R87.2, R224.1, R234.1, R235.1, R238.1, TP100.1, U12.6, U12.17, U12.30, U12.39, U12.52, U12.62, U12.72, U12.84, U12.95, U12.108, U12.121, U12.131, U12.143, U12.144, U23.22, U24.22, U27.5, U28.5
VMOT: C100.1, C101.1, C112.1, C113.1, C121.1, C122.1, C129.1, C130.1, C133.1, C134.1, C139.1, C140.1, C143.1, C144.1, D29.2, P49.1, Q1.6, Q2.6, Q3.6, Q4.6, Q5.6, Q6.6, Q7.2, R68.1, U31.29, U32.29
VMOT_IN: D9.1, D28.2, D29.1, D29.3, P18.1, R195.2
VMOT_SENSE: TP62.1, U12.13, U26.1, U26.2
VREF1: C16.1, C82.1, C83.1, FB1.1, U7.2, U31.24, U32.24
VSA1: R111.1, TP83.1, U12.26, U33.7
VSA1_RAW: C123.1, D19.3, R94.2, R117.2, R118.2
VSA2: R112.1, TP84.1, U12.29, U35.7
VSA2_RAW: C124.1, D20.3, R97.2, R119.2, R120.2
VSB1: R153.1, TP89.1, U12.27, U33.8
VSB1_RAW: C145.1, D21.3, R131.2, R156.2, R157.2
VSB2: R154.1, TP90.1, U12.44, U35.8
VSB2_RAW: C146.1, D22.3, R134.2, R158.2, R159.2
VSC1: R193.1, TP93.1, U12.28, U33.14
VSC1_RAW: C149.1, D25.3, R177.2, R189.2, R190.2
VSC2: R194.1, TP94.1, U12.45, U35.14
VSC2_RAW: C150.1, D26.3, R180.2, R191.2, R192.2

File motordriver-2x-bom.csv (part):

Title,Electric Motor Control Board
Revision,Rev A
Date,2019-02-02
Generated,Wed 06 Mar 2019 09:07:07 AM CET
Company,Swedish Embedded Group
Comment 1,Drawn by Martin Schröder
Comment 2,
Comment 3,
Comment 4,
Total Parts,659
Total Unique Parts,95



Ref,Qty,Value,Footprint,Availability,Comment,Description,LifeCycle,MPN,Price,Vendor,
C29 C35 C40 C42 C44 C48 C28 C34 C39 C41 C43 C47 C50 C3 C4 C16 C82 C83 C63 C61 C59 C62 C60 C17 C11 C12 C22 C25 C23 C26 C27 C24 C33 C31 C8 C93 C95 C96 C99 C102 C111 C114 C118 C86 C119 C117 C120 C30 C46 C10 C94 C36 C98 C97 C9 C21 C70 C151 C156 C154 C157 C155 C32 ,63,CAP_100nF_50V_0402,Capacitor_SMD:C_0402_1005Metric,120297 In Stock, ,Multilayer Ceramic Capacitors MLCC - SMD/SMT 100K pF 50Volts 10%,OK,CC0402KRX5R9BB104,0.087  EUR,Mouser
C6 C5 C13 C87 C91 C84 C88 C92 C85 C73 C77 C74 C75 C76 C78 C79 C80 C81 C7 C148 C147 C53 C56 C57 C37 C159 C160 C161 C162 C163 C164 C168 C170 C171 C51 ,35,CAP_2.2uF_16V_0402,Capacitor_SMD:C_0402_1005Metric,113017 In Stock, ,Multilayer Ceramic Capacitors MLCC - SMD/SMT 0402 16Vdc 2.2uF X6S 10%,OK,GRT155C81C225KE13D,0.271  EUR,Mouser
C1 C2 C14 C20 C125 C127 C131 C137 C126 C128 C132 C138 C72 C71 ,14,CAP_10pF_50V_0402,Capacitor_SMD:C_0402_1005Metric,383 In Stock, ,Multilayer Ceramic Capacitors MLCC - SMD/SMT WCAP-CSGP 10pF 0402 5% 50V MLCC,OK,885012005055,0.07  EUR,Mouser
C105 C106 C107 C123 C145 C149 C100 C108 C109 C110 C124 C146 C150 C101 ,14,CAP_100nF_100V_0603,Capacitor_SMD:C_0603_1608Metric,121849 In Stock, ,Multilayer Ceramic Capacitors MLCC - SMD/SMT 100K pF 10% 100 Volts,OK,CC0603KRX7R0BB104,0.183  EUR,Mouser
C115 C135 C116 C136 ,4,CAP_1nF_100V_0603,Capacitor_SMD:C_0603_1608Metric,100868 In Stock, ,Multilayer Ceramic Capacitors MLCC - SMD/SMT CGA 0603 100V 1000pF X7R 10% AEC-Q200,OK,CGA3E2X7R2A102K080AA,0.087  EUR,Mouser
C121 C129 C133 C103 C112 C122 C130 C134 C104 C113 C165 C167 ,12,CAP_2.2uF_100V_1210,Capacitor_SMD:C_1210_3225Metric,12161 In Stock, ,Multilayer Ceramic Capacitors MLCC - SMD/SMT 2.2uF 100V X7R 10% 1210 Flx AEC-Q200,OK,HMJ325AB7225KMHT,1.00  EUR,Mouser
C89 C90 ,2,CAP_0.022uF_100V_0603,Capacitor_SMD:C_0603_1608Metric,271764 In Stock, ,Multilayer Ceramic Capacitors MLCC - SMD/SMT 100V .022uF 0603 X7R 10%,OK,C0603C223K1RACTU,0.087  EUR,Mouser
C140 C143 C139 C144 C15 ,5,CAPP_220uF_63V_10x15_THT,Capacitor_THT:CP_Radial_D10.0mm_P5.00mm,2937 In Stock, ,Aluminium Electrolytic Capacitors - Radial Leaded 63V 220uF 85C 2k Hour Radial,OK,ESK227M063AH2AA,0.393  EUR,Mouser
C64 C66 C65 C67 C69 C68 C19 C166 ,8,CAP_100pF_50V_0402,Capacitor_SMD:C_0402_1005Metric,139976 On Order, ,Multilayer Ceramic Capacitors MLCC - SMD/SMT WCAP-CSGP 100pF 0402 10% 50V MLCC,OK,885012205055,0.03  EUR,Mouser
C141 C142 ,2,CAP_22nF_50V_0402,Capacitor_SMD:C_0402_1005Metric,76047 In Stock, ,Multilayer Ceramic Capacitors MLCC - SMD/SMT 0402 0.022uF 50volts X7R 5%,OK,GCM155R71H223JA55D,0.087  EUR,Mouser
C18 ,1,CAP_27nF_16V_0402,Capacitor_SMD:C_0402_1005Metric,10300 In Stock, ,Multilayer Ceramic Capacitors MLCC - SMD/SMT 0402 0.027uF 16volts X7R 10%,OK,GCM155R71C273KA37D,0.087  EUR,Mouser
C38 C169 ,2,CAPP_100uF_25V_6357,Capacitor_SMD:CP_Elec_6.3x5.7,25876 In Stock, ,Aluminium Electrolytic Capacitors - SMD 25 Volts 100uF 20% 6.3X5.7,OK,VZS101M1ETR-0606,0.335  EUR,Mouser
C52 C55 C58 C54 C152 ,5,CAP_22uF_10V_0805,Capacitor_SMD:C_0805_2012Metric,131798 In Stock, ,Multilayer Ceramic Capacitors MLCC - SMD/SMT 22uF 10V X5R +/-20% 0805 Gen Purp,OK,LMK212BBJ226MG-T,0.245  EUR,Mouser
C45 C49 ,2,CAP_10uF_25V_0805,Capacitor_SMD:C_0805_2012Metric,196753 In Stock, ,Multilayer Ceramic Capacitors MLCC - SMD/SMT 0805 10uF 25volts X5R 20%,OK,GRM21BR61E106MA73L,0.262  EUR,Mouser
D19 D21 D25 D20 D22 D26 D17 D18 D2 D1 D3 D4 D5 D6 D7 D8 ,16,D_BAT54S,Package_TO_SOT_SMD:SOT-23,388644 In Stock, ,Schottky Diodes & Rectifiers 30V 225mW Dual,OK,BAT54SLT1G,0.157  EUR,Mouser
D23 D24 ,2,D_TPD3E001,Package_TO_SOT_SMD:SOT-23-5,172970 In Stock, ,ESD Suppressors / TVS Diodes Low-Cap 3Ch ESD Protection Array,OK,TPD3E001DRLR,0.428  EUR,Mouser
D10 D11 D13 ,3,D_ESDCAN03,Package_TO_SOT_SMD:SOT-323_SC-70,20191 In Stock, ,ESD Suppressors / TVS Diodes Automotive dual-line Transil  Transient voltage suppressor (TVS) for CAN bus,New Product,ESDCAN03-2BWY ,0.367  EUR,Mouser
D12 D28 ,2,D_CDBC5100,Diode_SMD:D_SMC,9967 In Stock, ,Schottky Diodes & Rectifiers VR=100V  IO=5A (Halogen Free),OK,CDBC5100-HF,0.568  EUR,Mouser
D9 ,1,D_SMBJ48A,Diode_SMD:D_SMB,12398 In Stock, ,ESD Suppressors / TVS Diodes 600W 48V Unidirect,OK,SMBJ48A-TR,0.314  EUR,Mouser
D14 ,1,D_SMBJ12A,Diode_SMD:D_SMB,11297 In Stock, ,ESD Suppressors / TVS Diodes 600W 12V Unidirect,OK,SMBJ12A-TR,0.314  EUR,Mouser
D16 D30 ,2,D_SZ1SMB5913BT3G,Diode_SMD:D_SMB,2800 In Stock, ,Zener Diodes ZEN SMB REG 3W,OK,SZ1SMB5913BT3G,0.55  EUR,Mouser
D29 ,1,D_STPS41H100,Package_TO_SOT_SMD:TO-263-2,1484 In Stock, ,Schottky Diodes & Rectifiers Auto pwr Schottky 2X20A 100V 0.67VF,OK,STPS41H100CGY-TR,2.48  EUR,Mouser
D27 D32 D33 D15 ,4,D_BAT54,Diode_SMD:D_SOD-123,34404 In Stock, ,Schottky Diodes & Rectifiers BL Bipolar Discretes,OK,BAT54GWJ,0.122  EUR,Mouser
D31 ,1,LED_RED_0603,LED_SMD:LED_0603_1608Metric,4040 In Stock, ,Standard LEDs - SMD Red 630nm 90mcd 2V; 20mA; 0603,New Product,SML-D15VWT86C,0.367  EUR,Mouser
F1 ,1,FUSE_3A_9750,CUSTOM:Fuse_Littlefuse_9750,5709 In Stock, ,Surface Mount Fuses Fuseblock w/ fuse 3A OMNI BLOK 154,OK,0154003.DR,2.03  EUR,Mouser
F2 ,1,FUSE_4A_0603,Fuse:Fuse_0603_1608Metric,4945 In Stock, ,Surface Mount Fuses Fuse  Surface Mount 4A  0603 Size,New Product,0686F4000-01,0.262  EUR,Mouser
FB3 FB2 FB4 FB5 FB1 ,5,LB_220R_2A_0603,Inductor_SMD:L_0603_1608Metric,193480 In Stock, ,Ferrite Beads 220ohms GHz General Usage,OK,BLM18EG221SN1D,0.201  EUR,Mouser
GND1 ,1,GND_100X30,CUSTOM:GND_100X30, , , , , , , 
GND2 GND3 ,2,GND_MOTOR_DRIVER,CUSTOM:GND_MOTOR_DRIVER, , , , , , , 
GND4 ,1,GND_ANALOG_IN,CUSTOM:GND_ANALOG_IN, , , , , , , 
GND5 ,1,GND_ANALOG_OUT,CUSTOM:GND_ANALOG_OUT, , , , , , , 
J3 J2 ,2,CONN_RJ45_MAG,CUSTOM:RJ45_Tranformer,202 In Stock, ,Modular Connectors / Ethernet Connectors WE-RJ45 Intgtd XFMR 1x1 THT Tab Up,OK,7499010121A,5.72  EUR,Mouser
J1 ,1,USB_B_Micro,CUSTOM:USB_Micro-B_GCT_USB3076-30-A,80661 In Stock, ,USB Connectors 5P MICRO USB TYPE B RECEPTACLE W/ PEGS,OK,10118193-0001LF,0.384  EUR,Mouser
L1 ,1,L_33uH_4.2A_45mR,CUSTOM:L_Wuerth_WE-PD-Typ-LS_1250x1250,4062 In Stock, ,Fixed Inductors WE-PD 1210 33uH 4.2A .045Ohm,OK,7447709330,2.22  EUR,Mouser
L2 ,1,L_2.2uH_8A,Inductor_SMD:L_Coilcraft_XxL4020,31040 In Stock, ,Fixed Inductors 2.2uH 20% 8A 23.5mOhms AEC-Q200,OK,XFL4020-222MEC,1.93  EUR,Mouser
MT4 MT1 MT2 MT3 ,4,MOUNT_HOLE,MountingHole:MountingHole_3.2mm_M3_Pad, , , , ,#, , 
P17 ,1,CONN_DEBUG_2R,Connector_IDC:IDC-Header_2x05_P2.54mm_Vertical,11668 In Stock, ,Headers & Wire Housings 10P STRT SOLDER TAIL HIGH TEMP,OK,N2510-6002RB,1.22  EUR,Mouser
P47 P48 ,2,CONN_HALL,CUSTOM:CONN_HALL,587 In Stock, ,Pluggable Terminal Blocks WR-TBL Mod3221 3.5mm 5PIn Horzntl PCBHdr,OK,691322110005,1.00  EUR,Mouser
P37 P41 ,2,CONN_ENCODER,CUSTOM:CONN_ENCODER,760 In Stock, ,Pluggable Terminal Blocks WR-TBL Mod3221 3.5mm 8PIn Horzntl PCBHdr,OK,691322110008,1.25  EUR,Mouser
P38 P39 P40 P42 P43 P44 P13 P14 P15 P16 ,10,CONN_SENSOR,CUSTOM:CONN_SENSOR,2041 In Stock, ,Pluggable Terminal Blocks WR-TBL PCB Model3211 3Pin 3.5mm Vtcl,OK,691322110003,0.63  EUR,Mouser
P45 P46 ,2,CONN_MOTOR,CUSTOM:ANYTEK_7.62mm_2x_3P_32A,176 In Stock, ,Pluggable Terminal Blocks TB PLG SKT RA W/F,OK,VC0301500000G,1.01  EUR,Mouser
P9 P11 ,2,CONN_JOYSTICK,CUSTOM:CONN_JOYSTICK,792 In Stock, ,Pluggable Terminal Blocks WR-TBL PCB Model3221 4Pin 3.5mm Hztl,OK,691322110004,0.75  EUR,Mouser
P19 P20 P24 ,3,CONN_CAN,CUSTOM:CONN_CAN,2041 In Stock, ,Pluggable Terminal Blocks WR-TBL PCB Model3211 3Pin 3.5mm Vtcl,OK,691322110003,0.63  EUR,Mouser
P18 ,1,CONN_POWER_41A,CUSTOM:PhoenixContact_Power41A_2,5_2-G-7,62_1x02_P7.62mm_Horizontal,357 In Stock, ,Pluggable Terminal Blocks 2 Pos 7.62mm pitch Through Hole Header,OK,1720466,2.68  EUR,Mouser
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
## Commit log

2019-01-23 Add schematic
2019-01-23 add missing files
2019-01-25 update schematic and add footprints
2019-01-25 update schematic
2019-01-26 update encoder interface
2019-01-27 add test points and pmic to motor drive circuit
2019-01-28 add analog in
2019-01-29 add can and eeprom
2019-01-29 add switch input and gpio chip
2019-01-29 add ethercat interface
2019-01-29 add lcd connector
2019-01-29 work on the ethercat circuit
2019-01-30 add main power
2019-01-30 add power supplies
2019-01-30 cleanup schematic
2019-01-30 start connecting pins
2019-01-31 connect more pins to mcu, change opamp and add analog multiplexer
2019-01-31 change analog out to opamp output
2019-01-31 add opamps to voltage sensing
2019-01-31 add preamp for voltage sensing and add UEXT
2019-02-01 add gpio and connect most pins
2019-02-01 update annotated schematic
2019-02-01 start preliminary pcb layout
2019-02-01 fix footprints
2019-02-02 add break resistor circuit and simulation
2019-02-02 draft sent
2019-02-05 start reviewing the schematic
2019-02-11 review start
2019-02-11 continue schematic review: capacitors
2019-02-11 review diodes
2019-02-14 schematic review
2019-02-14 review footprints for switches and sensors
2019-02-15 component level review almost done on connectors
    Add a bunch of modified footprints and push latest schematic
2019-02-15 review most of the resistors
2019-02-15 finish resistor review
2019-02-16 ic review
2019-02-17 review power, eeprom and can txc
2019-02-17 review usb
2019-02-17 start designing power supply
2019-02-18 review power regulators
2019-02-18 component review done
2019-02-19 review labels
2019-02-19 finish review and drc
2019-02-19 update field values
2019-02-19 start component placement
2019-02-20 pcb layout
2019-02-20 optimize connector size
2019-02-20 place second motor driver
2019-02-21 review footprints and horizontal vertical stuff
2019-02-21 power supply layout
2019-02-21 cpu layout
2019-02-21 save latest schematic
2019-02-22 come up with pcb outline
2019-02-22 better placement
2019-02-22 create custom grounds
2019-02-23 update grounds and connectors
2019-02-25 start routing
2019-02-25 routing with fills
2019-02-25 fix many routing issues
2019-02-25 routing power supply
2019-02-26 update connectors
2019-02-26 update track widths
2019-02-26 continue layout of second drive
2019-02-27 continue routing
2019-02-27 fix rj45 and route ethercat
2019-02-28 more routing
2019-02-28 continue layout of cpu
2019-03-01 rewire bunch of control lines
2019-03-01 down to 35 unrouted nets
2019-03-01 down to 14 unrouted
2019-03-02 everything connected and courtyards updated
2019-03-03 review connections
2019-03-03 200 tracks reviewed
2019-03-03 312 done
2019-03-03 318 tracks done
2019-03-04 375 tracks done
2019-03-04 board done
2019-03-06 board finished
2019-03-06 add bom
2019-03-06 update fields
2019-03-07 update board to have proper layer window
2019-03-07 add gerbers
2019-03-07 update schematic plot
2019-03-07 move all footprints to custom library and push updates to schematic and pcb
2019-03-07 move unused footprints to my lib and remove CUSTOM
2019-03-07 rename block diagram
2019-03-14 minor fixes
2019-03-23 push fixes to pcb
2019-05-07 push latest files
2020-11-13 latest updates
2022-10-23 kicad: update to kicad v6
    Closes #2
2022-10-24 ci: add kibot build support
    Closes #3
2022-10-25 bom: add bom generation
    Closes #4
2022-10-27 cleanup: organize files and make sure we have all 3d models
    Related to #5
2022-10-28 readme: update information
    Closes #5
2022-10-29 readme: update with schematic and header
    Closes #7
